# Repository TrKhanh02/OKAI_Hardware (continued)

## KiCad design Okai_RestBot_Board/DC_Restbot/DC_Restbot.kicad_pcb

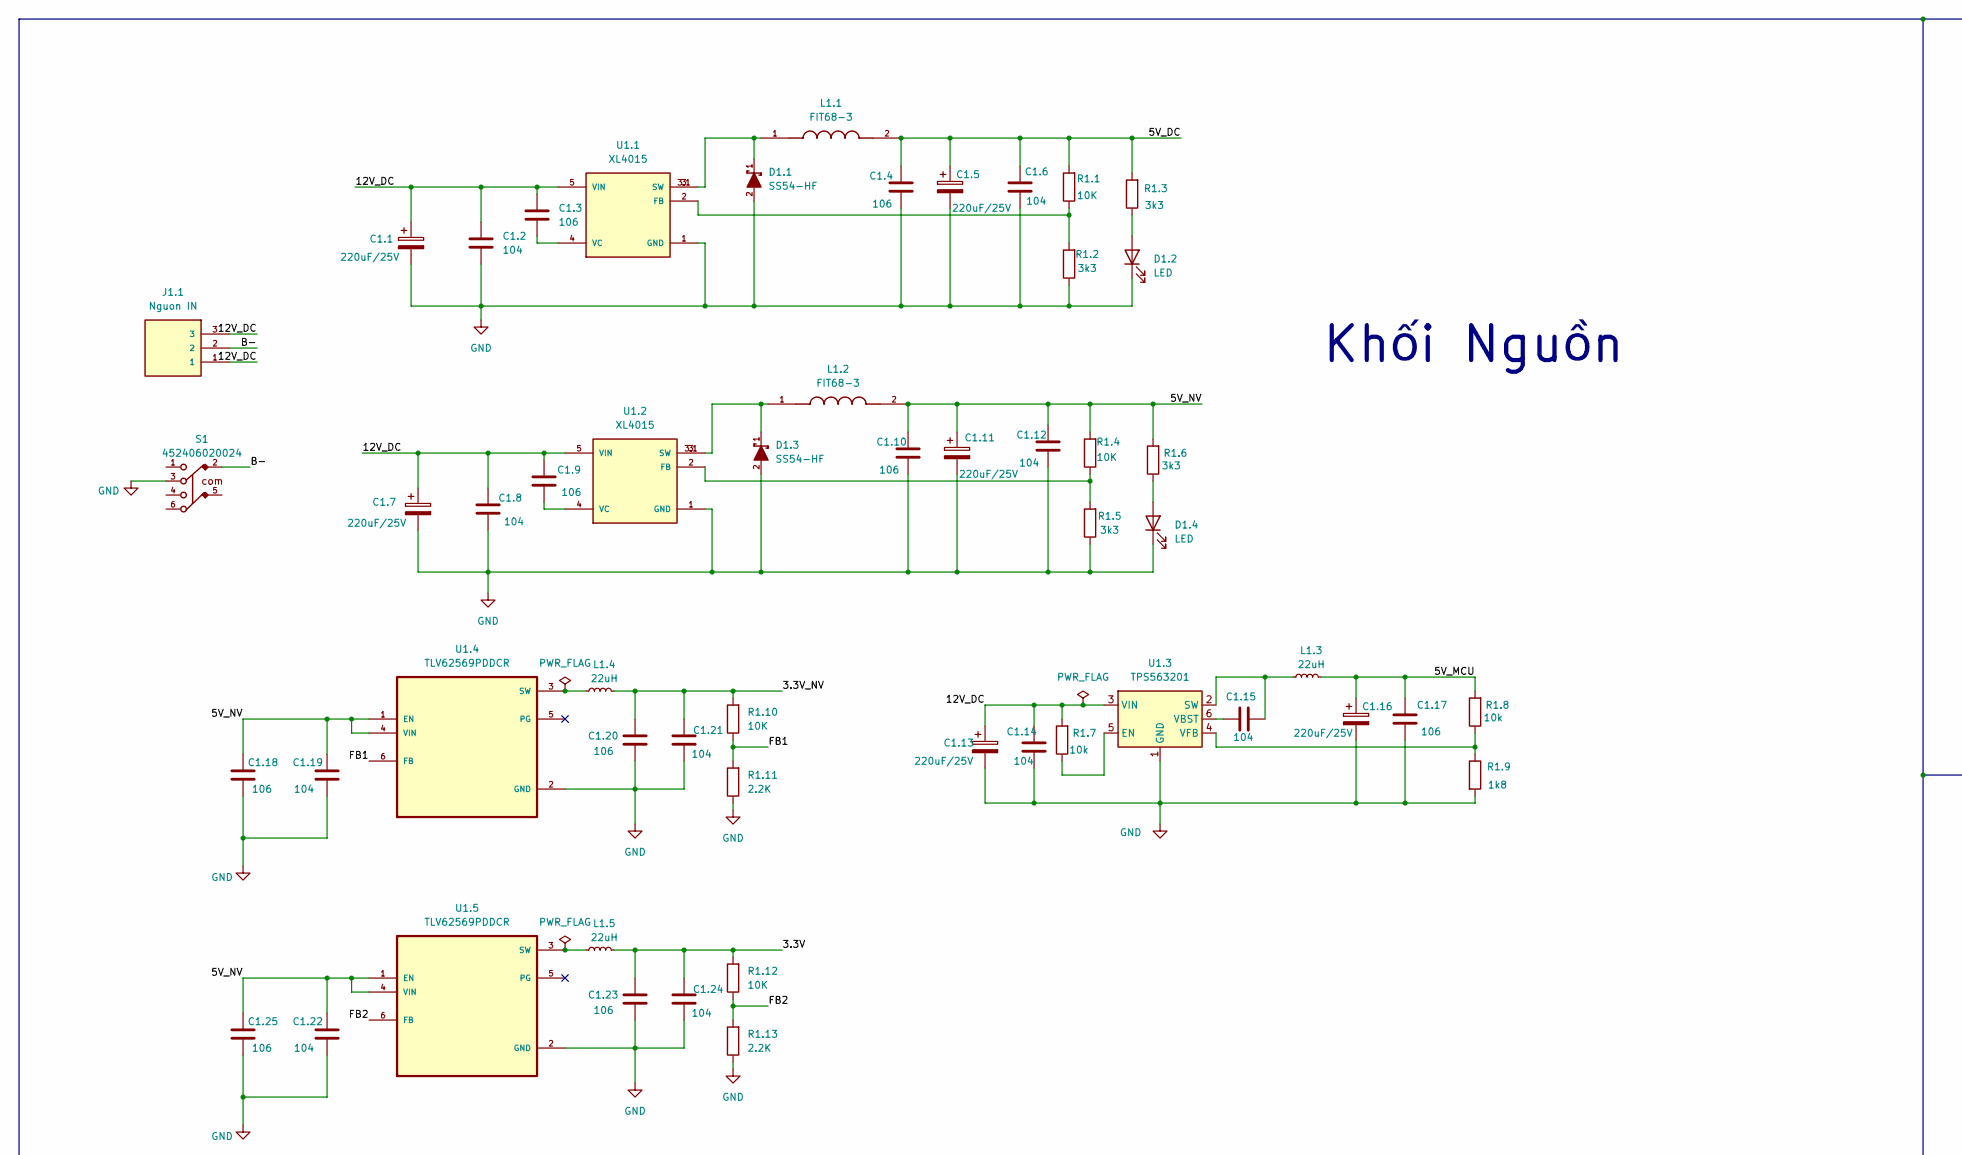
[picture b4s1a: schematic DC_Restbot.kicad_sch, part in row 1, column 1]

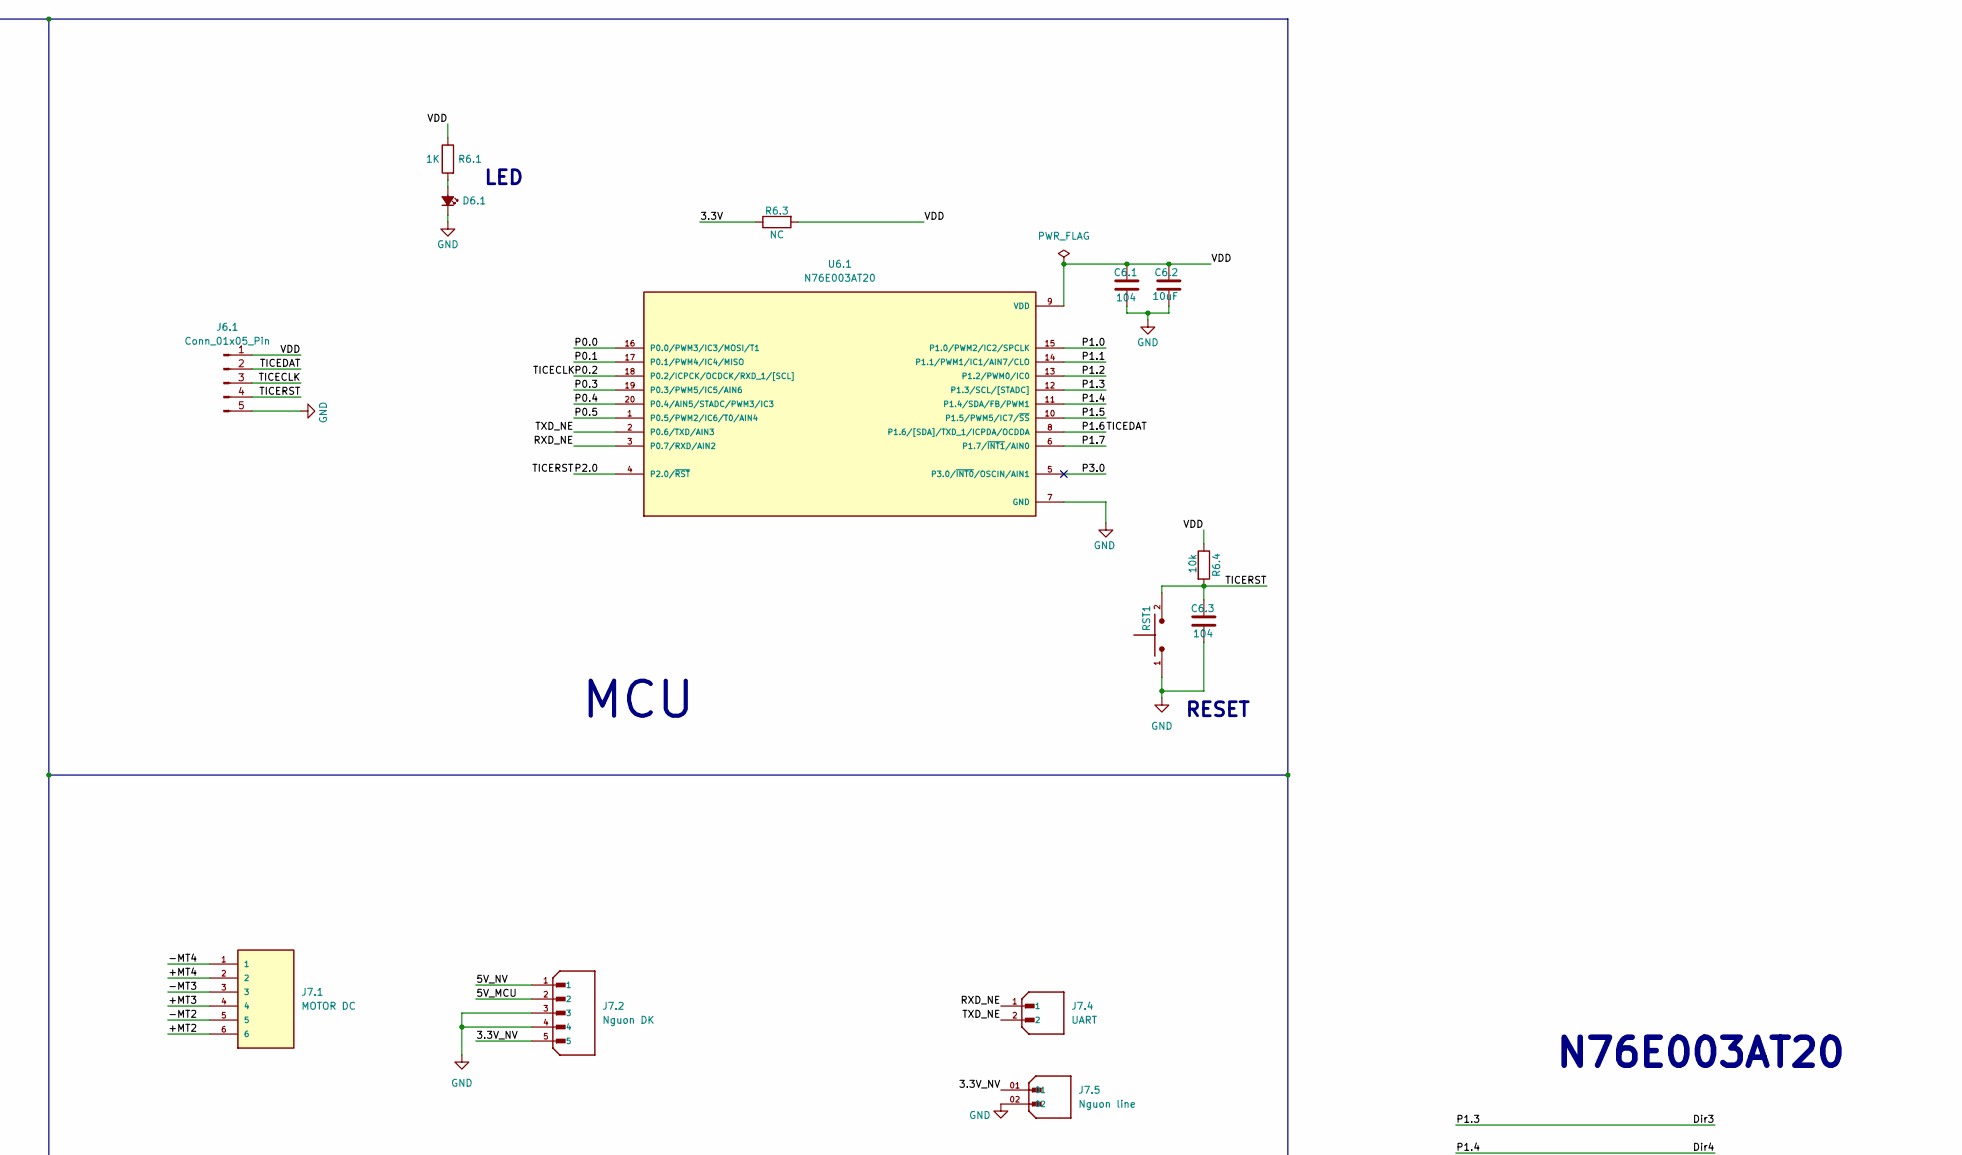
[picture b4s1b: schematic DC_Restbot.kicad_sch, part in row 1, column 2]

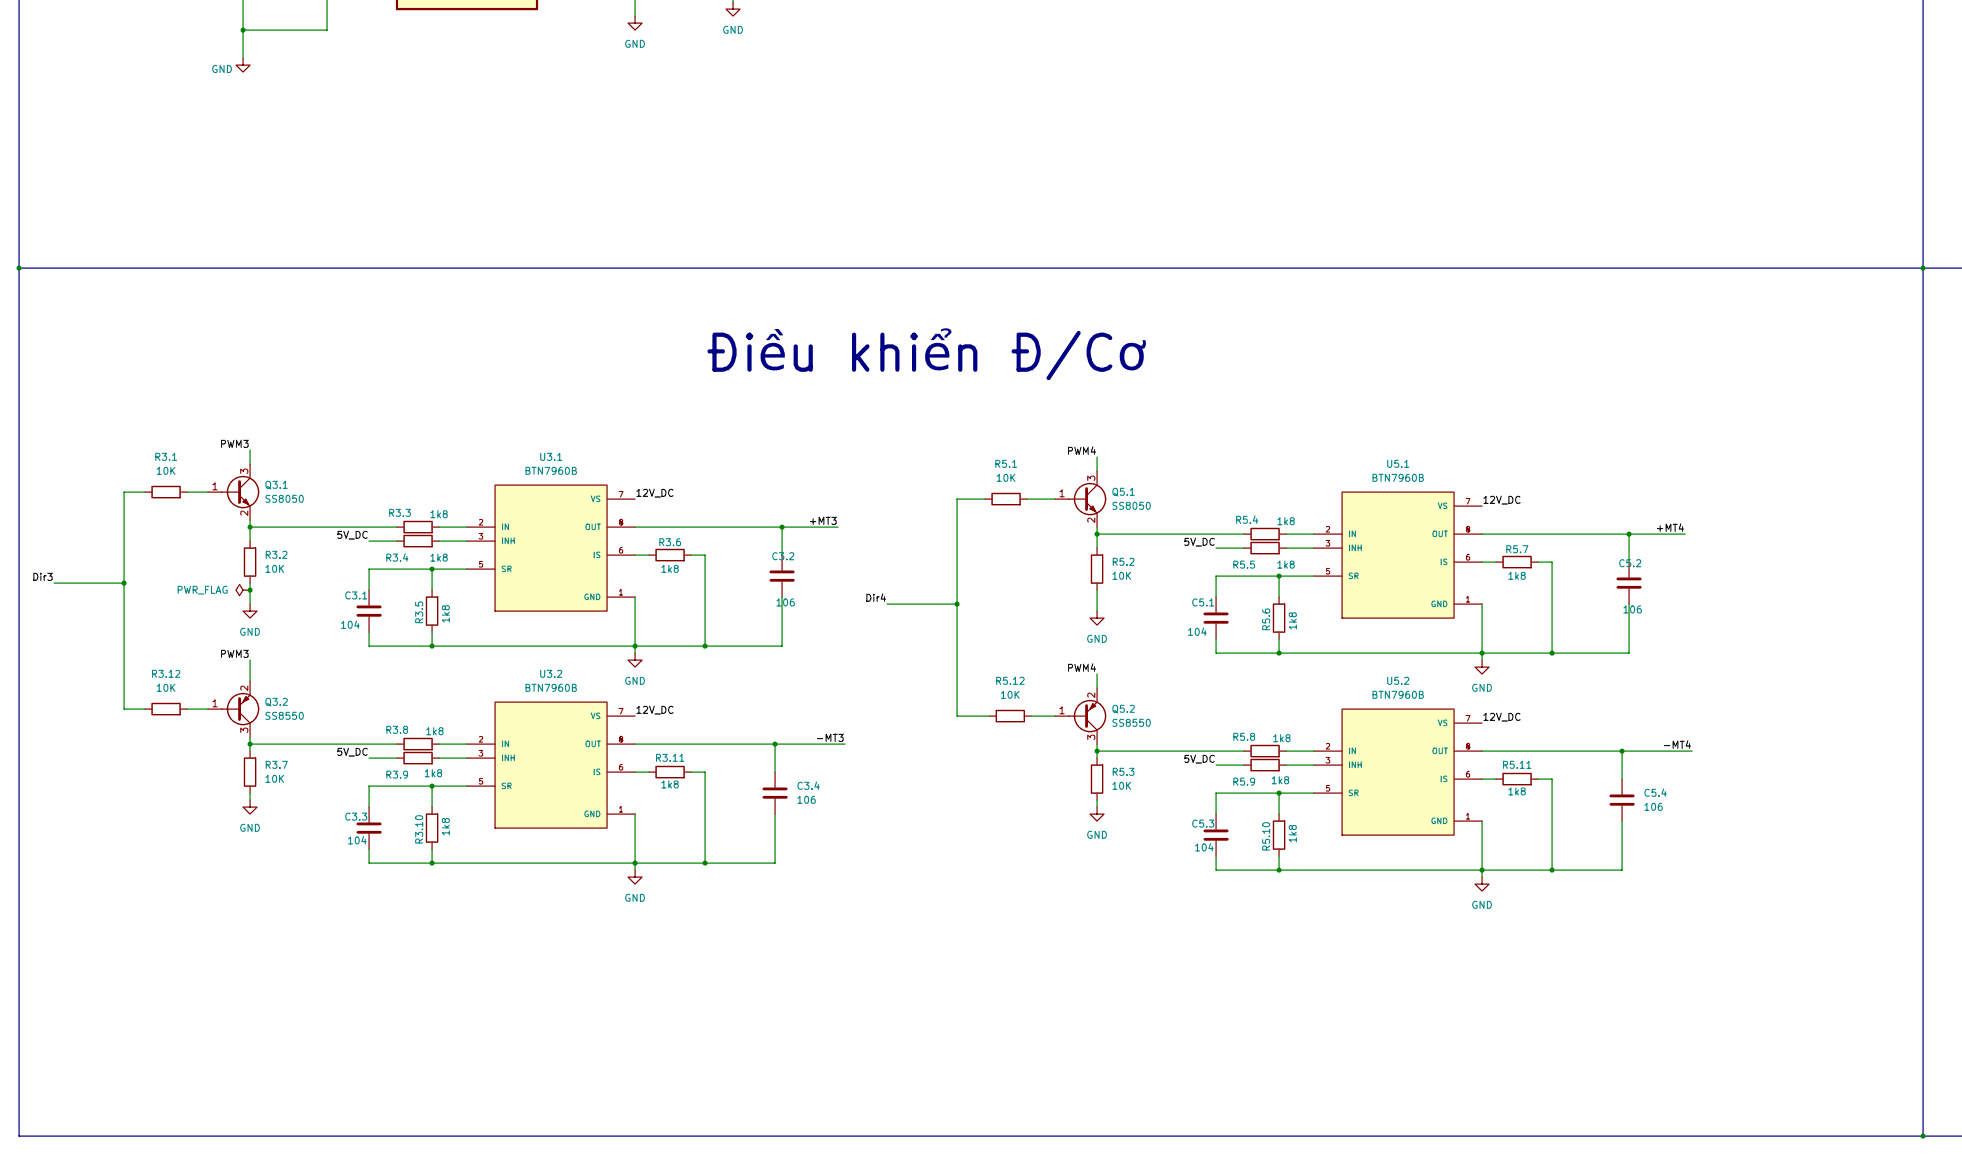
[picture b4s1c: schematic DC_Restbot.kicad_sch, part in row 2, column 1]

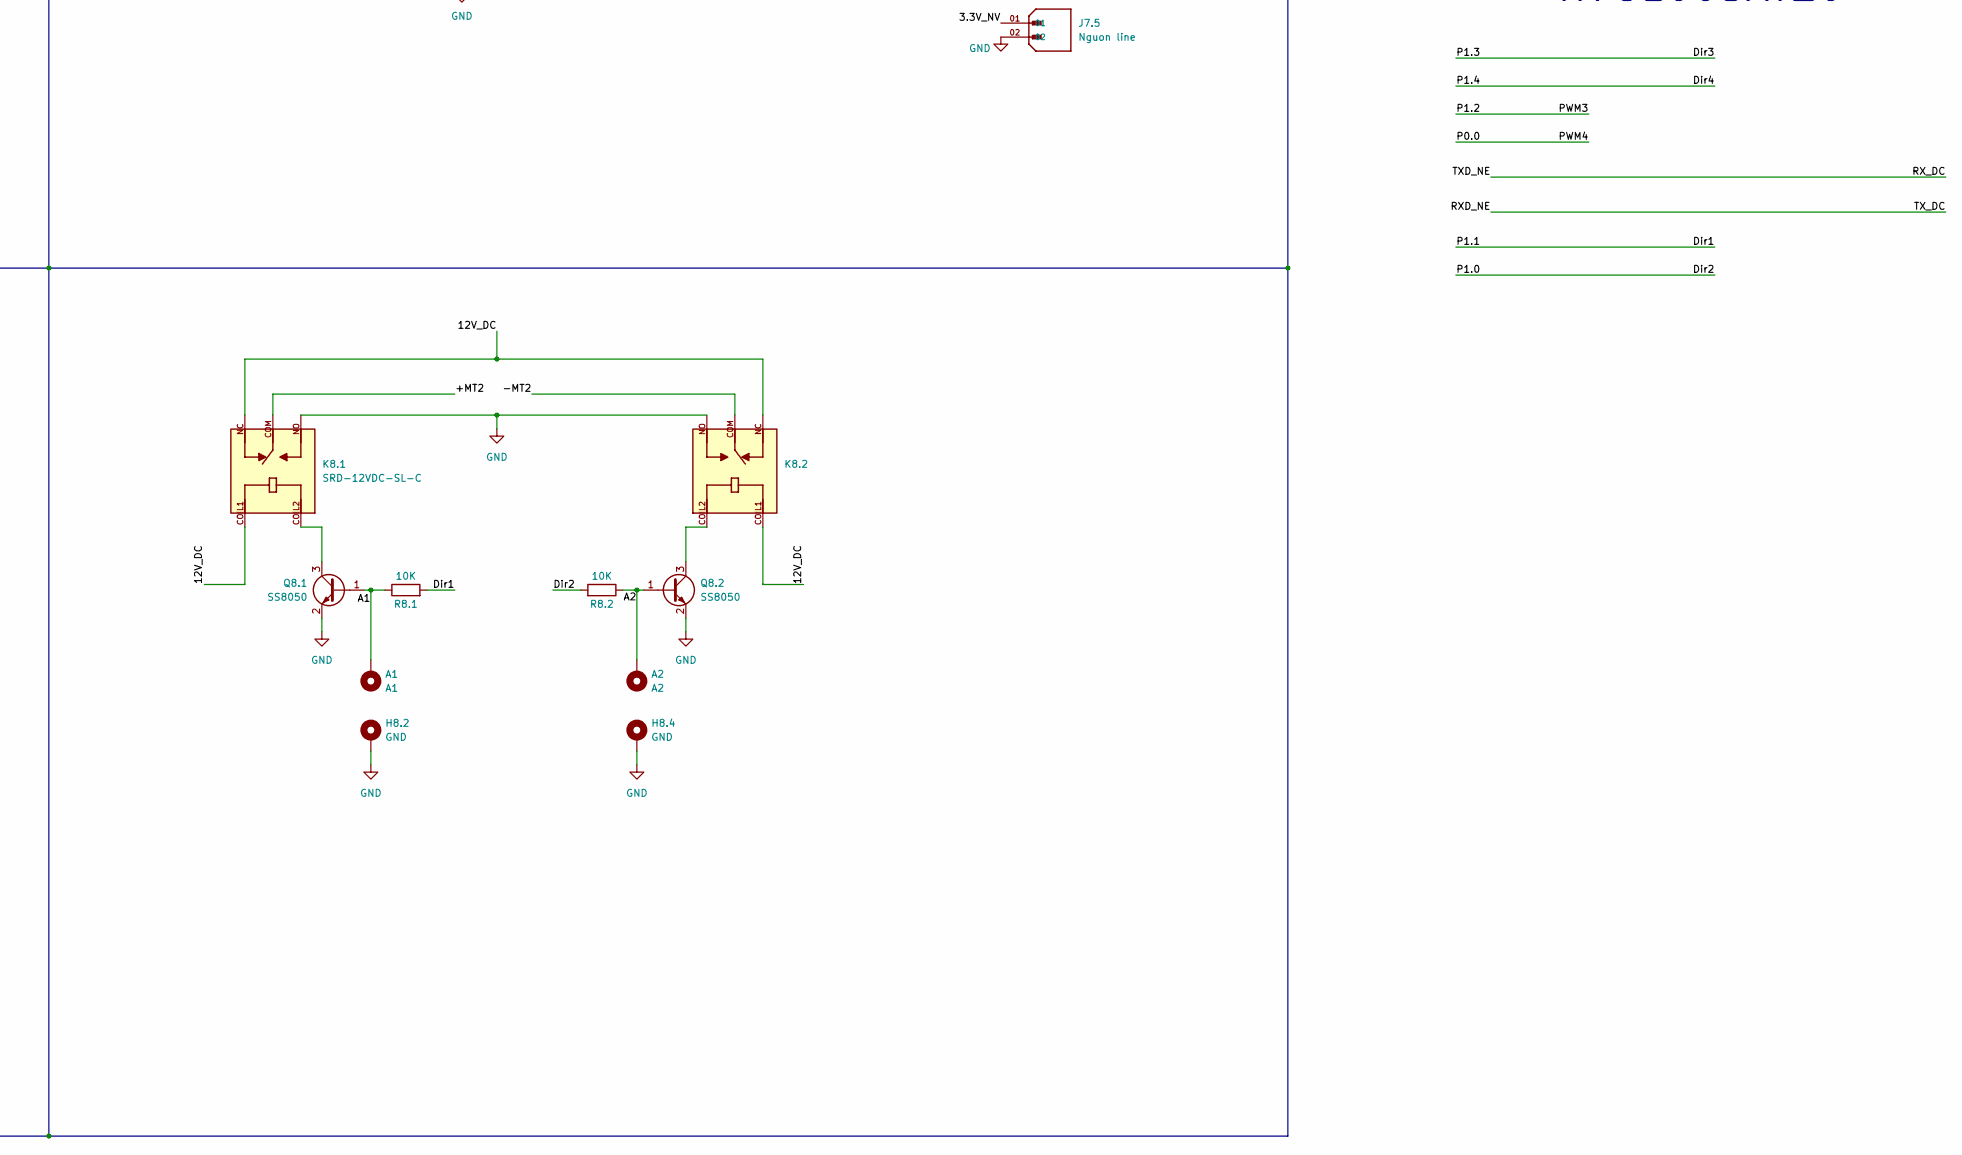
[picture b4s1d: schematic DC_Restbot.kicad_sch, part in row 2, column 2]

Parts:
A1: A1; MountingHole_2.5mm_Pad_TopBottom
A2: A2; MountingHole_2.5mm_Pad_TopBottom
C1.1, C1.5, C1.7, C1.11, C1.13, C1.16: 220uF/25V; CP_Elec_8x10.5
C1.2, C1.6, C1.8, C1.12, C1.14, C1.15, C1.19, C1.21, C1.22, C1.24, C3.1, C3.3, C5.1, C5.3: 104; C_0805_2012Metric
C1.3, C1.4, C1.9, C1.10, C1.17, C1.18, C1.20, C1.23, C1.25, C3.2, C3.4, C5.2, C5.4: 106; C_0805_2012Metric
C6.1, C6.3: 104; C_0805_2012Metric_Pad1.18x1.45mm_HandSolder
C6.2: 10uF; C_0805_2012Metric_Pad1.18x1.45mm_HandSolder
D1.1, D1.3: SS54-HF; DIOM5025X220N; MOUSER_PART_NUMBER 750-SS54-HF
D1.2, D1.4: LED; LED_0805_2012Metric
D6.1: LED_Small_Filled; LED_0805_2012Metric_Pad1.15x1.40mm_HandSolder
H8.2, H8.4: GND; MountingHole_2.5mm_Pad_TopBottom
J1.1: Nguon IN; CUI_TBP04R1-500-03BE; PARTREV 1.0
J6.1: Conn_01x05_Pin; PinHeader_1x05_P2.54mm_Vertical
J7.1: MOTOR DC; CUI_TBP04R1-500-06BE; PARTREV 1.0
J7.2: Nguon DK; JST_B5B-XH-A; PARTREV 7/4/21
J7.4: UART; JST_B2B-XH-A_LF__SN_; PARTREV N/A
J7.5: Nguon line; VALCON_VH396-02S-010; PARTREV A1
K8.1, K8.2: SRD-12VDC-SL-C; RELAY_SRD-12VDC-SL-C; PARTREV 1.0
L1.1, L1.2: FIT68-3; IND_FIT68-3; PARTREV N/A
L1.3, L1.4, L1.5: 22uH; L_Ferrocore_DLG-0705
Q3.1, Q5.1, Q8.1, Q8.2: SS8050; SOT-23
Q3.2, Q5.2: SS8550; SOT-23
R1.1, R1.4, R1.10, R1.12: 10K; R_0805_2012Metric
R1.2, R1.3, R1.5, R1.6: 3k3; R_0805_2012Metric
R1.7, R1.8: 10k; R_0805_2012Metric
R1.9, R3.3, R3.4, R3.5, R3.6, R3.8, R3.9, R3.10, R3.11, R5.4, R5.5, R5.6, R5.7, R5.8, R5.9, R5.10, R5.11: 1k8; R_0805_2012Metric
R1.11, R1.13: 2.2K; R_0805_2012Metric
R3.1, R3.2, R3.7, R3.12, R5.1, R5.2, R5.3, R5.12, R8.1, R8.2: 10K; R_0805_2012Metric_Pad1.20x1.40mm_HandSolder
R6.1: 1K; R_0805_2012Metric_Pad1.20x1.40mm_HandSolder
R6.3: NC; R_0805_2012Metric_Pad1.20x1.40mm_HandSolder
R6.4: 10k; R_0805_2012Metric_Pad1.20x1.40mm_HandSolder
RST1: TS10-63-26-BE-250-SMT-TR; SW_TS10-63-26-BE-250-SMT-TR; PARTREV 1.0
S1: 452406020024
U1.1, U1.2: XL4015; CONV_XL4015; PARTREV 1.5
U1.3: TPS563201; SOT-23-6
U1.4, U1.5: TLV62569PDDCR; SOT95P280X110-6N
U3.1, U3.2, U5.1, U5.2: BTN7960B; DPAK127P1490X440-8N; PARTREV 1.1
U6.1: N76E003AT20; SOP65P640X120-20N; PARTREV 1.04

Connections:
/3.3V: C1.23.1, C1.24.1, L1.5.1, R1.12.2, R6.3.1
/3.3V_NV: C1.20.1, C1.21.1, J7.2.5, J7.5.01, L1.4.1, R1.10.2
/5V_DC: C1.4.1, C1.5.1, C1.6.1, L1.1.2, R1.1.2, R1.3.2, R3.4.1, R3.9.1, R5.5.1, R5.9.1
/5V_MCU: C1.16.1, C1.17.1, J7.2.2, L1.3.1, R1.8.2
/5V_NV: C1.10.1, C1.11.1, C1.12.1, C1.18.1, C1.19.1, C1.22.1, C1.25.1, J7.2.1, L1.2.2, R1.4.2, R1.6.2, U1.4.1 (EN), U1.4.4 (VIN), U1.5.1 (EN), U1.5.4 (VIN)
/12V_DC: C1.1.1, C1.2.1, C1.3.1, C1.7.1, C1.8.1, C1.9.1, C1.13.1, C1.14.1, J1.1.1, J1.1.3, K8.1.COIL1, K8.1.NC, K8.2.COIL1, K8.2.NC, R1.7.2, U1.1.5 (VIN), U1.2.5 (VIN), U1.3.3 (VIN), U3.1.7 (VS), U3.2.7 (VS), U5.1.7 (VS), U5.2.7 (VS)
/+MT2: J7.1.6, K8.1.COM
/+MT3: C3.2.2, J7.1.4, U3.1.4 (OUT), U3.1.8 (OUT)
/+MT4: C5.2.2, J7.1.2, U5.1.4 (OUT), U5.1.8 (OUT)
/-MT2: J7.1.5, K8.2.COM
/-MT3: C3.4.2, J7.1.3, U3.2.4 (OUT), U3.2.8 (OUT)
/-MT4: C5.4.2, J7.1.1, U5.2.4 (OUT), U5.2.8 (OUT)
/A1: A1.1, Q8.1.1 (B), R8.1.1
/A2: A2.1, Q8.2.1 (B), R8.2.1
/B-: J1.1.2, S1.2
/Dir1: R8.1.2, U6.1.14 (P1.1/PWM1/IC1/AIN7/CLO)
/Dir2: R8.2.2, U6.1.15 (P1.0/PWM2/IC2/SPCLK)
/Dir3: R3.1.1, R3.12.1, U6.1.12 (P1.3/SCL/[STADC])
/Dir4: R5.1.1, R5.12.1, U6.1.11 (P1.4/SDA/FB/PWM1)
/FB1: R1.10.1, R1.11.2, U1.4.6 (FB)
/FB2: R1.12.1, R1.13.2, U1.5.6 (FB)
/P0.0: Q5.1.3 (C), Q5.2.2 (E), U6.1.16 (P0.0/PWM3/IC3/MOSI/T1)
/P0.1: U6.1.17 (P0.1/PWM4/IC4/MISO)
/P0.2: J6.1.3, U6.1.18 (P0.2/ICPCK/OCDCK/RXD_1/[SCL])
/P0.3: U6.1.19 (P0.3/PWM5/IC5/AIN6)
/P0.4: U6.1.20 (P0.4/AIN5/STADC/PWM3/IC3)
/P0.5: U6.1.1 (P0.5/PWM2/IC6/T0/AIN4)
/P1.2: Q3.1.3 (C), Q3.2.2 (E), U6.1.13 (P1.2/PWM0/IC0)
/P1.5: U6.1.10 (P1.5/PWM5/IC7/~SS)
/P1.6: J6.1.2, U6.1.8 (P1.6/[SDA]/TXD_1/ICPDA/OCDDA)
/P1.7: U6.1.6 (P1.7/~INT1/AIN0)
/P2.0: C6.3.1, J6.1.4, R6.4.2, RST1.2, U6.1.4 (P2.0/~RST)
/P3.0: U6.1.5 (P3.0/~INT0/OSCIN/AIN1)
/RXD_NE: J7.4.1, U6.1.3 (P0.7/RXD/AIN2)
/RX_DC: J7.4.2, U6.1.2 (P0.6/TXD/AIN3)
/VDD: C6.1.1, C6.2.1, J6.1.1, R6.1.1, R6.3.2, R6.4.1, U6.1.9 (VDD)
GND: C1.1.2, C1.2.2, C1.4.2, C1.5.2, C1.6.2, C1.7.2, C1.8.2, C1.10.2, C1.11.2, C1.12.2, C1.13.2, C1.14.2, C1.16.2, C1.17.2, C1.18.2, C1.19.2, C1.20.2, C1.21.2, C1.22.2, C1.23.2, C1.24.2, C1.25.2, C3.1.1, C3.2.1, C3.3.1, C3.4.1, C5.1.1, C5.2.1, C5.3.1, C5.4.1, C6.1.2, C6.2.2, C6.3.2, D1.1.2, D1.2.1 (K), D1.3.2, D1.4.1 (K), D6.1.1 (K), H8.2.1, H8.4.1, J6.1.5, J7.2.3, J7.2.4, J7.5.02, K8.1.NO, K8.2.NO, Q8.1.2 (E), Q8.2.2 (E), R1.2.1, R1.5.1, R1.9.2, R1.11.1, R1.13.1, R3.2.1, R3.5.1, R3.6.2, R3.7.1, R3.10.1, R3.11.2, R5.2.1, R5.3.1, R5.6.1, R5.7.2, R5.10.1, R5.11.2, RST1.1, S1.3, U1.1.1 (GND), U1.2.1 (GND), U1.3.1 (GND), U1.4.2 (GND), U1.5.2 (GND), U3.1.1 (GND), U3.2.1 (GND), U5.1.1 (GND), U5.2.1 (GND), U6.1.7 (GND)
unnamed: D1.1.1, L1.1.1, U1.1.3 (SW), U1.1.3.1 (SW)
unnamed: D1.2.2 (A), R1.3.1
unnamed: D1.3.1, L1.2.1, U1.2.3 (SW), U1.2.3.1 (SW)
unnamed: D1.4.2 (A), R1.6.1
unnamed: D6.1.2 (A), R6.1.2
unnamed: Q3.1.1 (B), R3.1.2
unnamed: Q3.1.2 (E), R3.2.2, R3.3.1
unnamed: Q3.2.1 (B), R3.12.2
unnamed: Q3.2.3 (C), R3.7.2, R3.8.1
unnamed: Q5.1.1 (B), R5.1.2
unnamed: Q5.1.2 (E), R5.2.2, R5.4.1
unnamed: Q5.2.1 (B), R5.12.2
unnamed: Q5.2.3 (C), R5.3.2, R5.8.1
unnamed: K8.1.COIL2, Q8.1.3 (C)
unnamed: K8.2.COIL2, Q8.2.3 (C)
unnamed: R1.1.1, R1.2.2, U1.1.2 (FB)
unnamed: C1.3.2, U1.1.4 (VC)
unnamed: R1.4.1, R1.5.2, U1.2.2 (FB)
unnamed: C1.9.2, U1.2.4 (VC)
unnamed: R1.7.1, U1.3.5 (EN)
unnamed: C1.15.2, L1.3.2, U1.3.2 (SW)
unnamed: C1.15.1, U1.3.6 (VBST)
unnamed: R1.8.1, R1.9.1, U1.3.4 (VFB)
unnamed: L1.4.2, U1.4.3 (SW)
unnamed: L1.5.2, U1.5.3 (SW)
unnamed: R3.3.2, U3.1.2 (IN)
unnamed: R3.4.2, U3.1.3 (INH)
unnamed: R3.6.1, U3.1.6 (IS)
unnamed: C3.1.2, R3.5.2, U3.1.5 (SR)
unnamed: R3.8.2, U3.2.2 (IN)
unnamed: R3.9.2, U3.2.3 (INH)
unnamed: R3.11.1, U3.2.6 (IS)
unnamed: C3.3.2, R3.10.2, U3.2.5 (SR)
unnamed: R5.4.2, U5.1.2 (IN)
unnamed: R5.5.2, U5.1.3 (INH)
unnamed: R5.7.1, U5.1.6 (IS)
unnamed: C5.1.2, R5.6.2, U5.1.5 (SR)
unnamed: R5.8.2, U5.2.2 (IN)
unnamed: R5.9.2, U5.2.3 (INH)
unnamed: R5.11.1, U5.2.6 (IS)
unnamed: C5.3.2, R5.10.2, U5.2.5 (SR)

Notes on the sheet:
MCU
Khối Nguồn
LED
N76E003AT20
RESET
Điều khiển Đ/Cơ

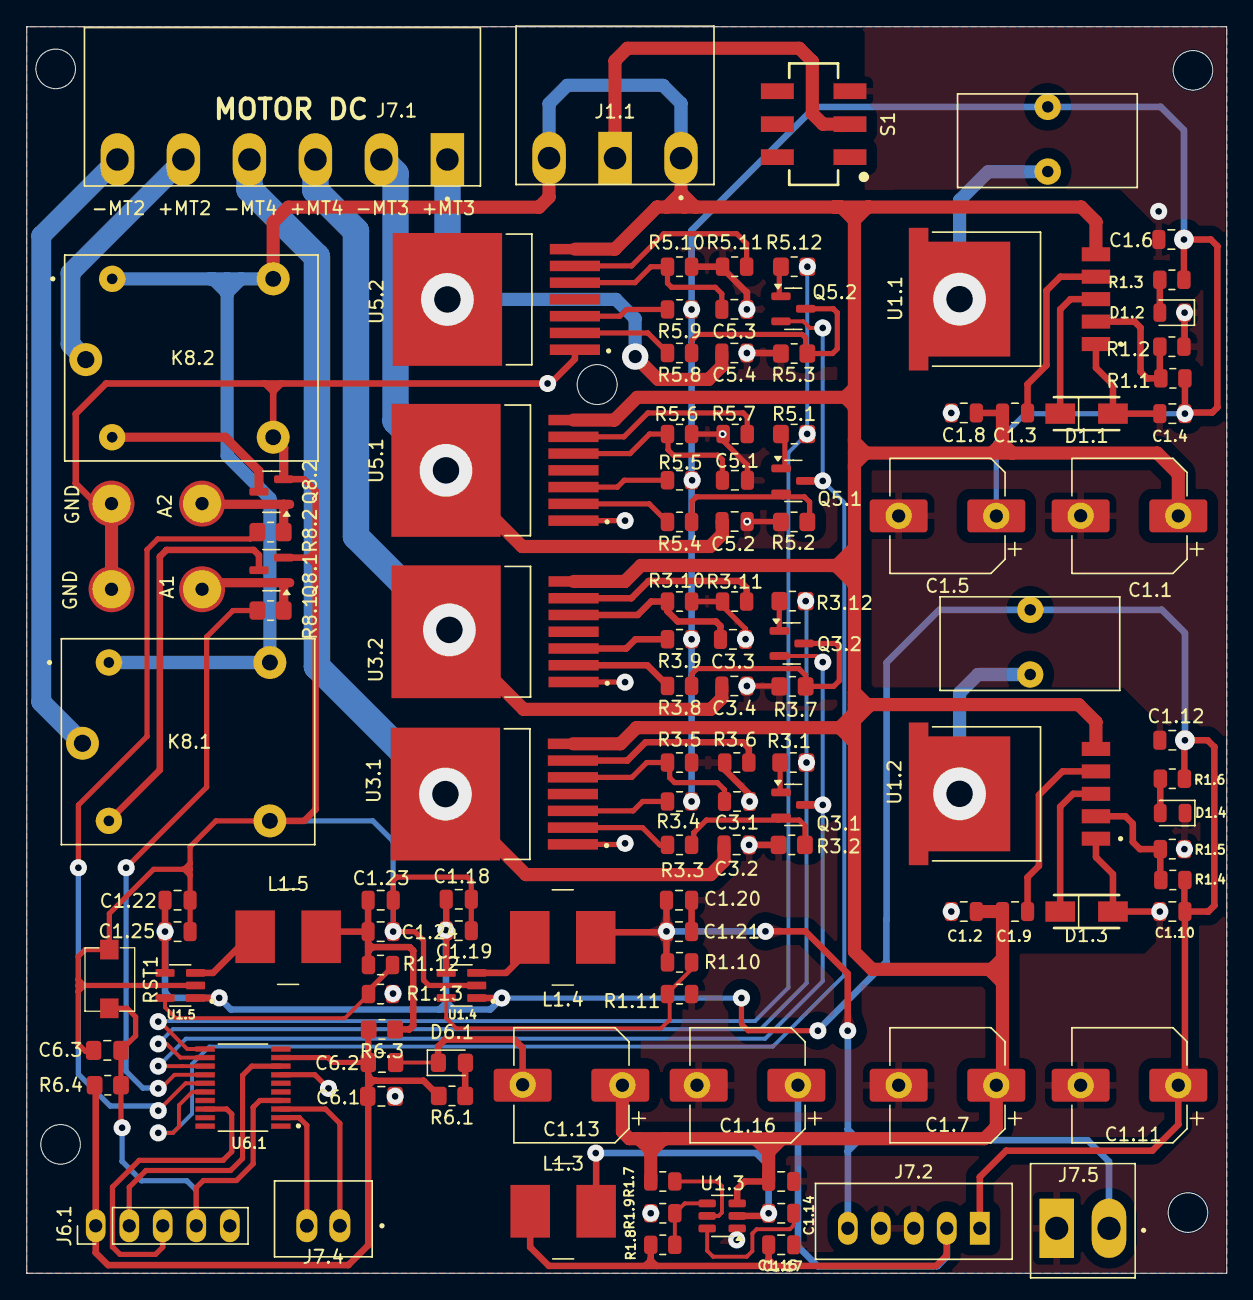
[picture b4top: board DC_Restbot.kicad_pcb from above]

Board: 2 copper layers, 90.9 x 94.5 mm, 118 parts (0 on the bottom side), 71 nets.

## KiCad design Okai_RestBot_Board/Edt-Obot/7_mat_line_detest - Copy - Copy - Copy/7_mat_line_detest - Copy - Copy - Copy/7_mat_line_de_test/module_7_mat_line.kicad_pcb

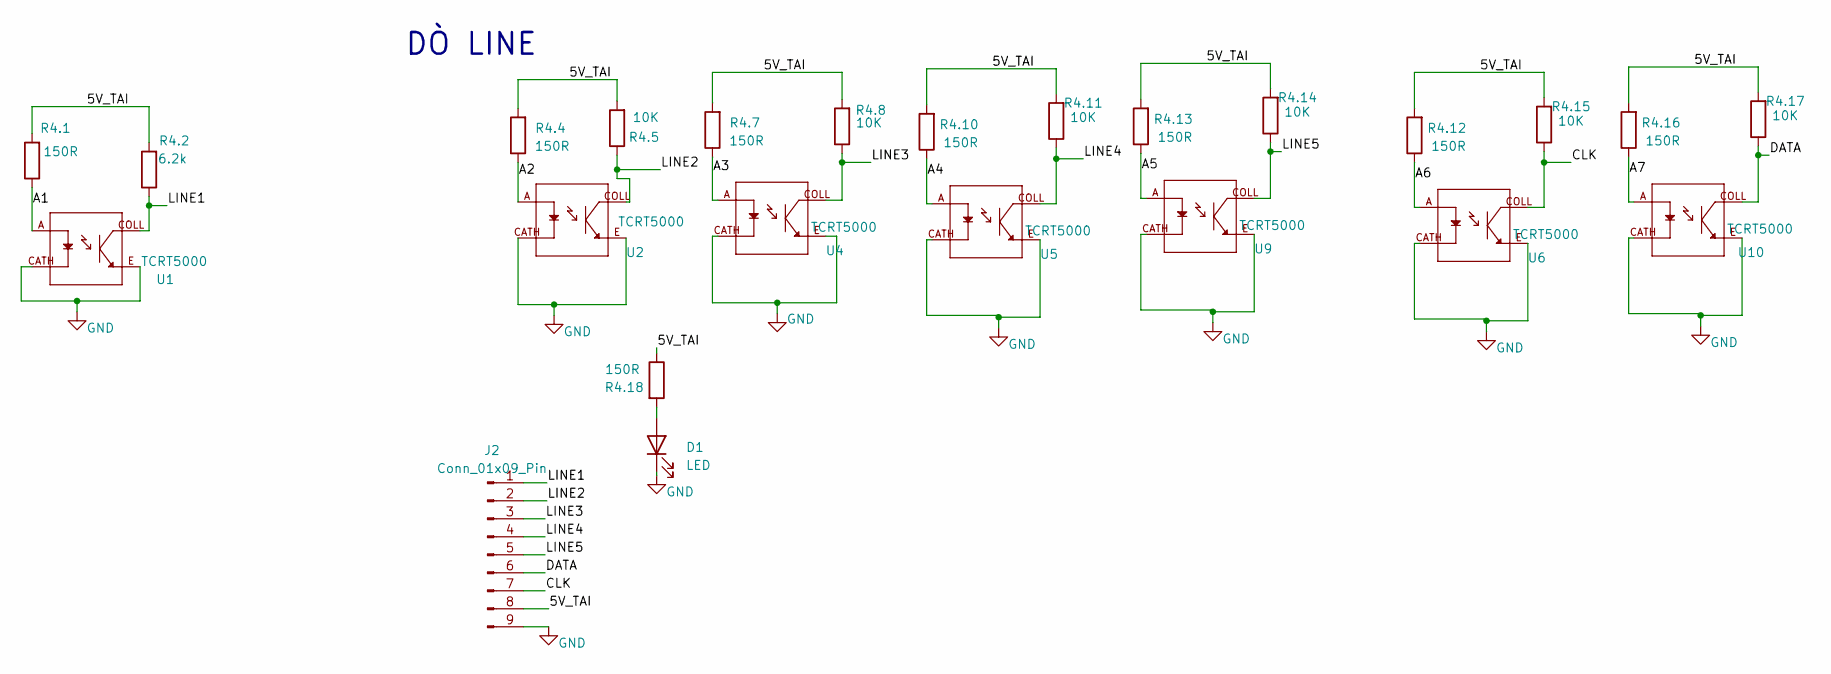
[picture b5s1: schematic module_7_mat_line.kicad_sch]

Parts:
D1: LED; LED_0805_2012Metric
J2: Conn_01x09_Pin; PinHeader_1x09_P2.54mm_Vertical
R4.1, R4.4, R4.7, R4.10, R4.12, R4.13, R4.16, R4.18: 150R; R_0805_2012Metric
R4.2: 6.2k; R_0805_2012Metric
R4.5, R4.8, R4.11, R4.14, R4.15, R4.17: 10K; R_0805_2012Metric
U1, U2, U4, U5, U6, U9, U10: TCRT5000; OPTO_TCRT5000; PARTREV 1.7

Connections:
/5V_TAI: J2.8, R4.1.2, R4.2.2, R4.4.2, R4.5.2, R4.7.2, R4.8.2, R4.10.2, R4.11.2, R4.12.2, R4.13.2, R4.14.2, R4.15.2, R4.16.2, R4.17.2, R4.18.1
/A1: R4.1.1, U1.A
/A2: R4.4.1, U2.A
/A3: R4.7.1, U4.A
/A4: R4.10.1, U5.A
/A5: R4.13.1, U9.A
/A6: R4.12.1, U6.A
/A7: R4.16.1, U10.A
/CLK: J2.7, R4.15.1, U6.COLL
/DATA: J2.6, R4.17.1, U10.COLL
/LINE1: J2.1, R4.2.1, U1.COLL
/LINE2: J2.2, R4.5.1, U2.COLL
/LINE3: J2.3, R4.8.1, U4.COLL
/LINE4: J2.4, R4.11.1, U5.COLL
/LINE5: J2.5, R4.14.1, U9.COLL
GND: D1.1 (K), J2.9, U1.CATH, U1.E, U2.CATH, U2.E, U4.CATH, U4.E, U5.CATH, U5.E, U6.CATH, U6.E, U9.CATH, U9.E, U10.CATH, U10.E
unnamed: D1.2 (A), R4.18.2

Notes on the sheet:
DÒ LINE

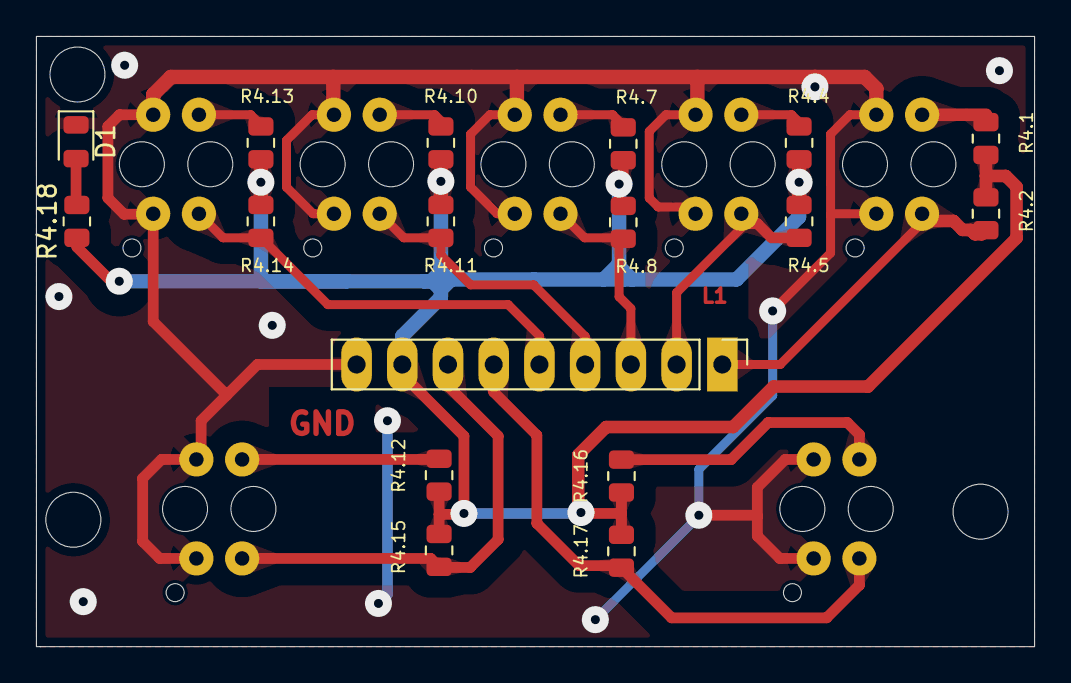
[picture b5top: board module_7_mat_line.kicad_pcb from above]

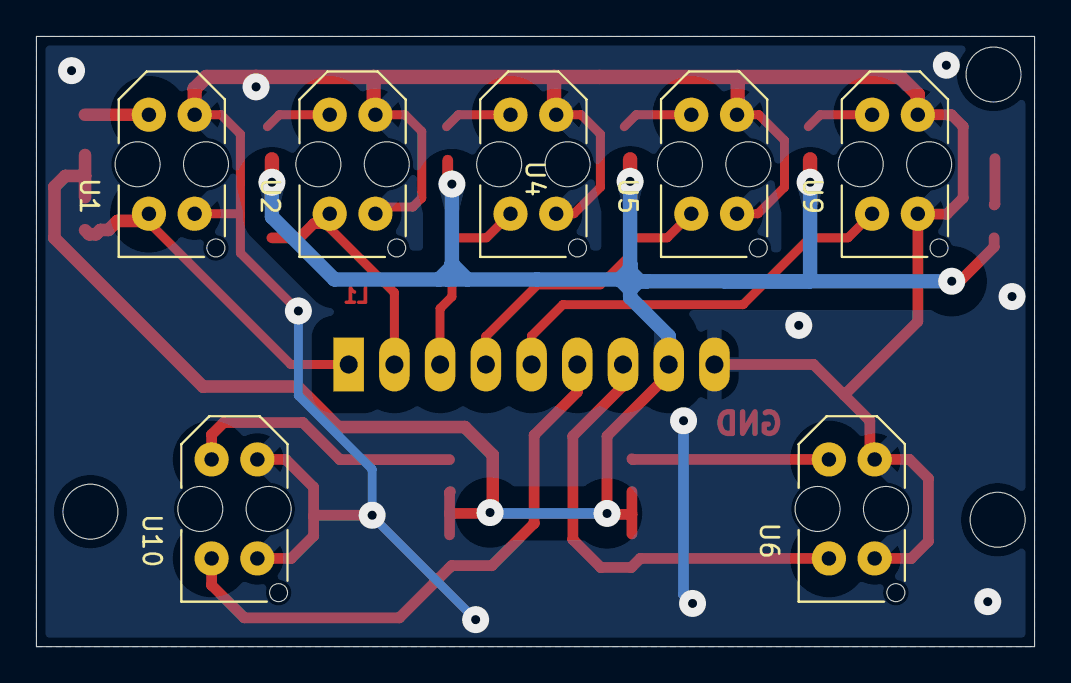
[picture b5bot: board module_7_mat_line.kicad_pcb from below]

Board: 2 copper layers, 55.4 x 33.9 mm, 24 parts (7 on the bottom side), 17 nets.

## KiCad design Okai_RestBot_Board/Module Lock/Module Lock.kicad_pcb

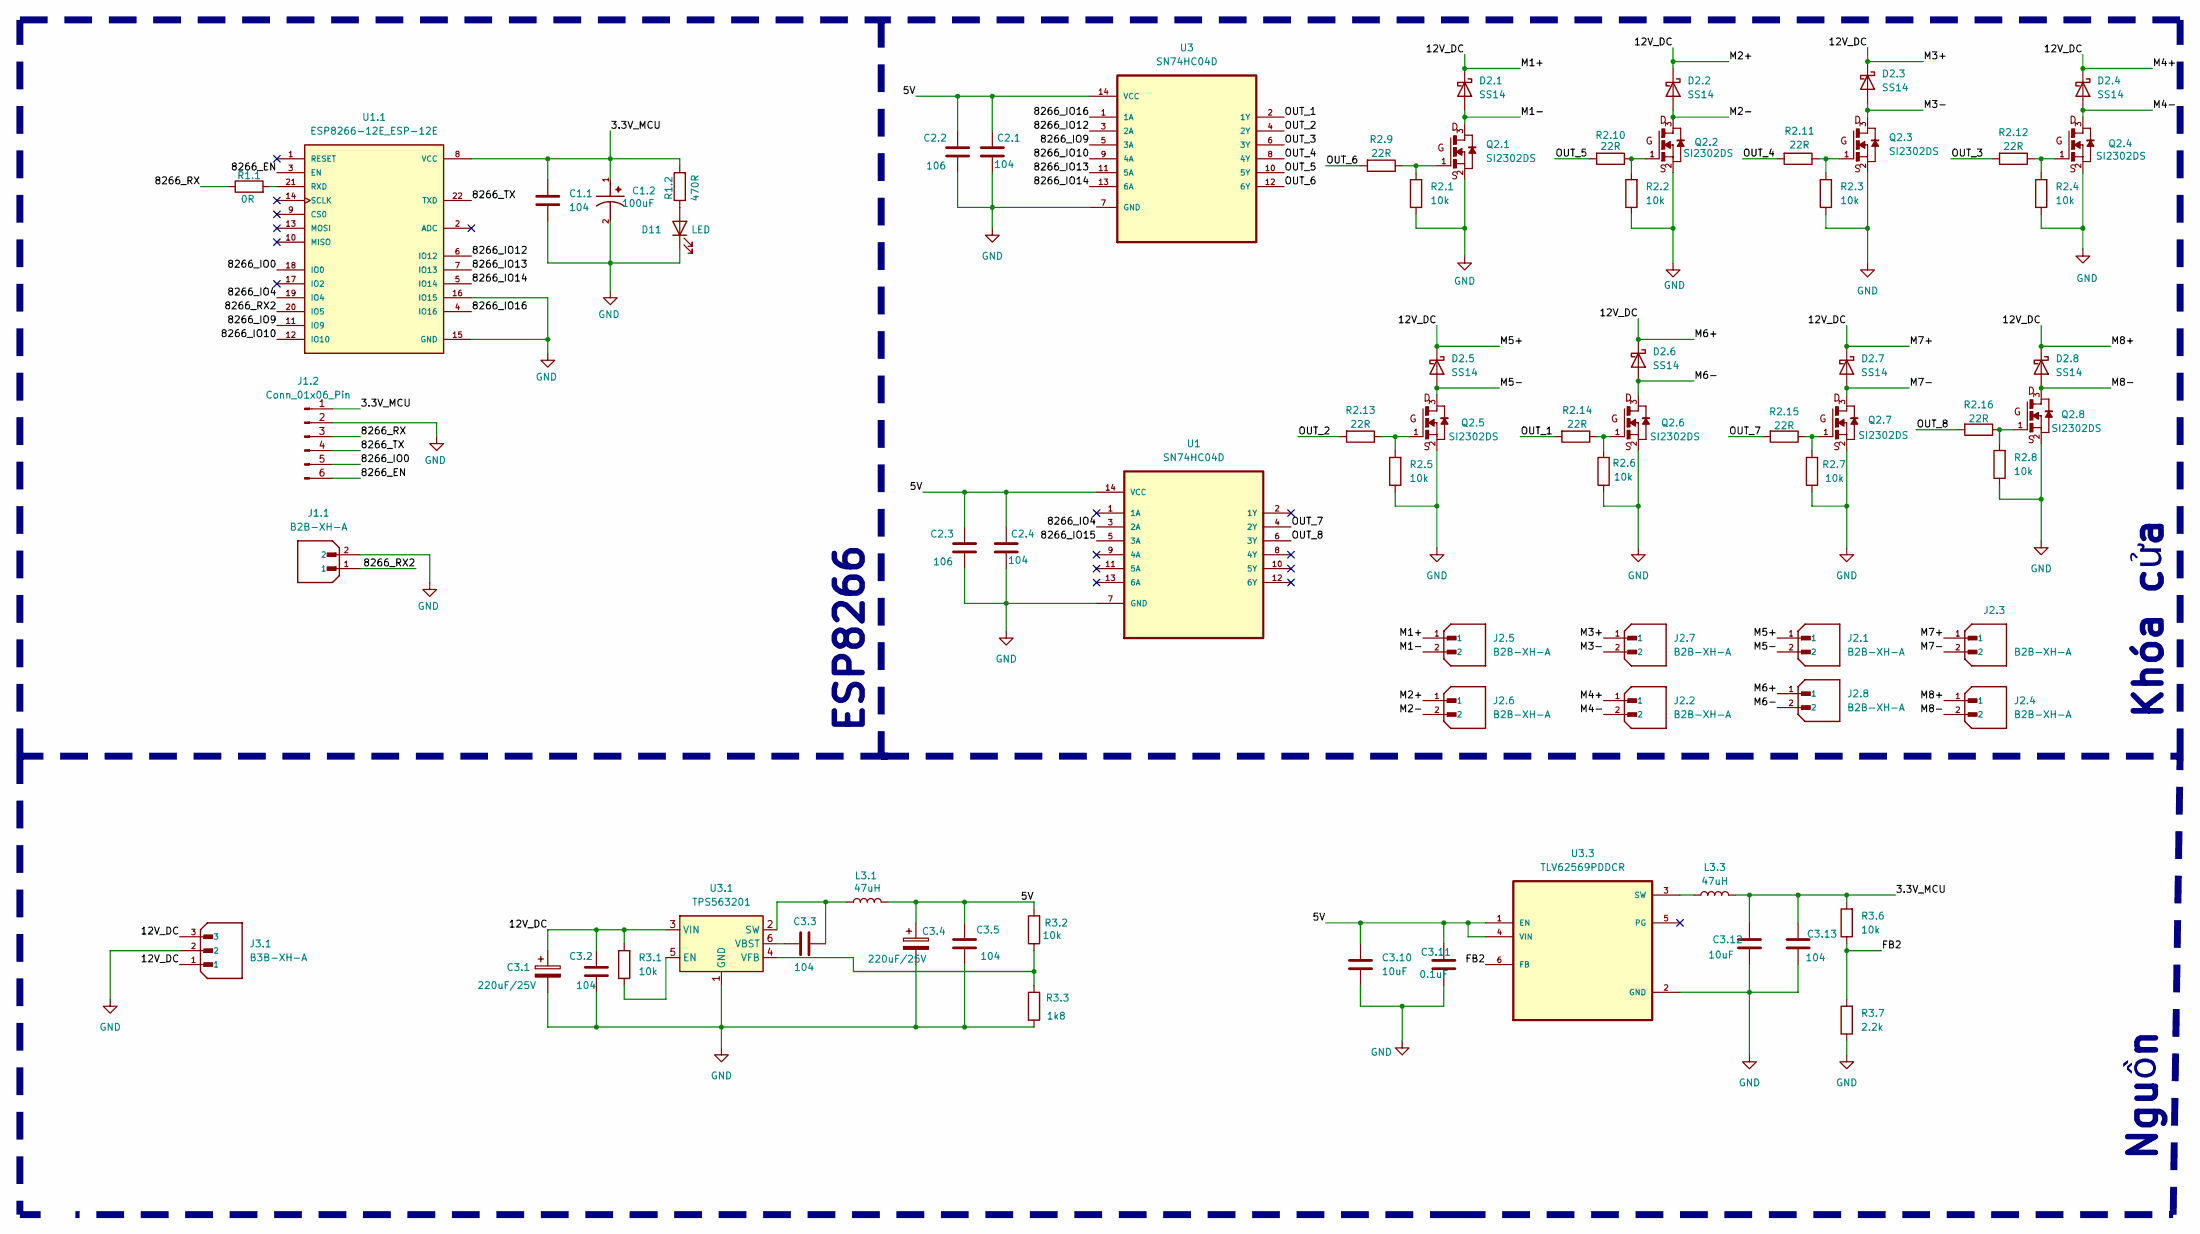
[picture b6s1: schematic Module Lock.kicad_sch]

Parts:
C1.1, C2.1, C2.4, C3.2, C3.3, C3.5, C3.13: 104; C_0805_2012Metric
C1.2: 100uF; CAPMP3216X180N; PARTREV 031320
C2.2, C2.3: 106; C_0805_2012Metric
C3.1, C3.4: 220uF/25V; CP_Elec_8x10.5
C3.10, C3.12: 10uF; C_0805_2012Metric
C3.11: 0.1uF; C_0805_2012Metric
D2.1, D2.2, D2.3, D2.4, D2.5, D2.6, D2.7, D2.8: SS14; D_SMA
D11: LED; LED_0805_2012Metric
J1.1, J2.1, J2.2, J2.3, J2.4, J2.5, J2.6, J2.7, J2.8: B2B-XH-A; JST_B2B-XH-A; PARTREV N/A
J1.2: Conn_01x06_Pin; PinHeader_1x06_P2.54mm_Vertical
J3.1: B3B-XH-A; JST_B3B-XH-A; PARTREV 7/4/21
L3.1, L3.3: 47uH; L_7.3x7.3_H4.5
Q2.1, Q2.2, Q2.3, Q2.4, Q2.5, Q2.6, Q2.7, Q2.8: SI2302DS; SOT23-3_TO-236AB
R1.1: 0R; R_0805_2012Metric_Pad1.20x1.40mm_HandSolder
R1.2: 470R; R_0805_2012Metric
R2.1, R2.2, R2.3, R2.4, R2.5, R2.6, R2.7, R2.8, R3.1, R3.2, R3.6: 10k; R_0805_2012Metric
R2.9, R2.10, R2.11, R2.12, R2.13, R2.14, R2.15, R2.16: 22R; R_0805_2012Metric
R3.3: 1k8; R_0805_2012Metric
R3.7: 2.2k; R_0805_2012Metric
U1, U3: SN74HC04D; SOIC127P600X175-14N
U1.1: ESP8266-12E_ESP-12E; XCVR_ESP8266-12E_ESP-12E
U3.1: TPS563201; SOT-23-6
U3.3: TLV62569PDDCR; SOT95P280X110-6N

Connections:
/3.3V_MCU: C1.1.1, C1.2.1, C3.12.1, C3.13.1, J1.2.1, L3.3.1, R1.2.2, R3.6.2, U1.1.8 (VCC)
/5V: C2.1.1, C2.2.1, C2.3.1, C2.4.1, C3.4.1, C3.5.1, C3.10.1, C3.11.1, L3.1.2, R3.2.2, U1.14 (VCC), U3.14 (VCC), U3.3.1 (EN), U3.3.4 (VIN)
/12V_DC: C3.1.1, C3.2.1, D2.1.1 (K), D2.2.1 (K), D2.3.1 (K), D2.4.1 (K), D2.5.1 (K), D2.6.1 (K), D2.7.1 (K), D2.8.1 (K), J2.1.1, J2.2.1, J2.3.1, J2.4.1, J2.5.1, J2.6.1, J2.7.1, J2.8.1, J3.1.1, J3.1.3, R3.1.2, U3.1.3 (VIN)
/8266_EN: J1.2.6, U1.1.3 (EN)
/8266_IO0: J1.2.5, U1.1.18 (IO0)
/8266_IO4: U1.3 (2A), U1.1.19 (IO4)
/8266_IO9: U1.1.11 (IO9), U3.5 (3A)
/8266_IO10: U1.1.12 (IO10), U3.9 (4A)
/8266_IO12: U1.1.6 (IO12), U3.3 (2A)
/8266_IO13: U1.1.7 (IO13), U3.11 (5A)
/8266_IO14: U1.1.5 (IO14), U3.13 (6A)
/8266_IO16: U1.1.4 (IO16), U3.1 (1A)
/8266_RX: J1.2.3, R1.1.1
/8266_RX2: J1.1.1, U1.1.20 (IO5)
/8266_TX: J1.2.4, U1.1.22 (TXD)
/FB2: R3.6.1, R3.7.2, U3.3.6 (FB)
/M1-: D2.1.2 (A), J2.5.2, Q2.1.3
/M2-: D2.2.2 (A), J2.6.2, Q2.2.3
/M3-: D2.3.2 (A), J2.7.2, Q2.3.3
/M4-: D2.4.2 (A), J2.2.2, Q2.4.3
/M5-: D2.5.2 (A), J2.1.2, Q2.5.3
/M6-: D2.6.2 (A), J2.8.2, Q2.6.3
/M7-: D2.7.2 (A), J2.3.2, Q2.7.3
/M8-: D2.8.2 (A), J2.4.2, Q2.8.3
/OUT_1: R2.14.2, U3.2 (1Y)
/OUT_2: R2.13.2, U3.4 (2Y)
/OUT_3: R2.12.2, U3.6 (3Y)
/OUT_4: R2.11.2, U3.8 (4Y)
/OUT_5: R2.10.2, U3.10 (5Y)
/OUT_6: R2.9.2, U3.12 (6Y)
/OUT_7: R2.15.2, U1.4 (2Y)
/OUT_8: R2.16.2, U1.6 (3Y)
unnamed: D11.2 (A), R1.2.1
unnamed: Q2.1.1, R2.1.2, R2.9.1
unnamed: Q2.2.1, R2.2.2, R2.10.1
unnamed: Q2.3.1, R2.3.2, R2.11.1
unnamed: Q2.4.1, R2.4.2, R2.12.1
unnamed: Q2.5.1, R2.5.2, R2.13.1
unnamed: Q2.6.1, R2.6.2, R2.14.1
unnamed: Q2.7.1, R2.7.2, R2.15.1
unnamed: Q2.8.1, R2.8.2, R2.16.1
unnamed: R1.1.2, U1.1.21 (RXD)
unnamed: R3.1.1, U3.1.5 (EN)
unnamed: C3.3.2, L3.1.1, U3.1.2 (SW)
unnamed: C3.3.1, U3.1.6 (VBST)
unnamed: R3.2.1, R3.3.1, U3.1.4 (VFB)
unnamed: L3.3.2, U3.3.3 (SW)

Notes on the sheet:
ESP8266
Nguồn
Khóa cửa

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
